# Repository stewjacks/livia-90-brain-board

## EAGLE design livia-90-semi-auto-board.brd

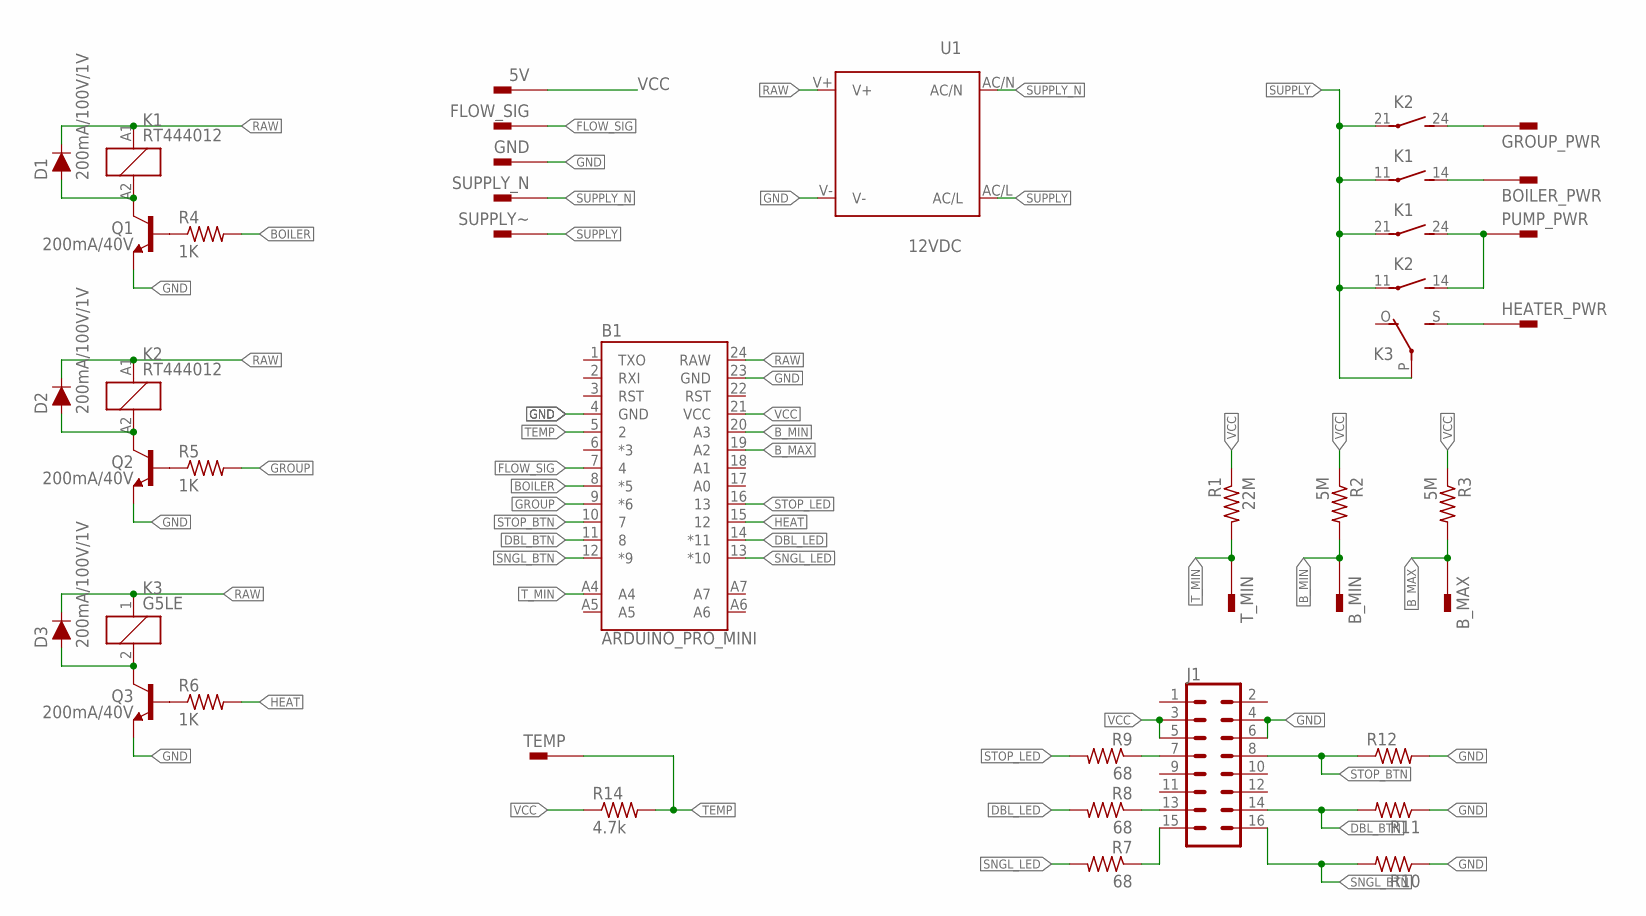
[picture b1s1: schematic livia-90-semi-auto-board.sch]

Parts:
5V: PIN2F061.040; F061.040
B1: ARDUINO_PRO_MINI
BOILER_PWR: PIN2F061.040; F061.040
B_MAX: PIN2F061.040; F061.040
B_MIN: PIN2F061.040; F061.040
D1, D2, D3: 200mA/100V/1V; DIODE-1N4148
FLOW_SIG: PIN2F061.040; F061.040
GND: PIN2F061.040; F061.040
GROUP_PWR: PIN2F061.040; F061.040
HEATER_PWR: PIN2F061.040; F061.040
J1: CONN_08X2; 2X8
K1, K2: RT444012; RT2N/O
K3: G5LE
PUMP_PWR: PIN2F061.040; F061.040
Q1, Q2, Q3: 200mA/40V; TO-92
R1: 22M; 0207/7
R2, R3: 5M; 0207/7
R4, R5, R6: 1K; 0207/7
R7, R8, R9: 68; 0207/7
R10, R11, R12: R-US_0207/7; 0207/7
R14: 4.7k; 0207/7
SUPPLY_N: PIN2F061.040; F061.040
SUPPLY~: PIN2F061.040; F061.040
TEMP: PIN2F061.040; F061.040
T_MIN: PIN2F061.040; F061.040
U1: 12VDC; IRM_05/10

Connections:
BOILER: B1.8 (*5), R4.2
B_MAX: B1.19 (A2), B_MAX.A1, B_MAX.A2, R3.2
B_MIN: B1.20 (A3), B_MIN.A1, B_MIN.A2, R2.2
DBL_BTN: B1.11 (8), J1.14, R11.2
DBL_LED: B1.14 (*11), R8.2
FLOW_SIG: B1.7 (4), FLOW_SIG.A1, FLOW_SIG.A2
GND: B1.4 (GND), B1.23 (GND), GND.A1, GND.A2, J1.4, J1.6, Q1.1 (E), Q2.1 (E), Q3.1 (E), R10.1, R11.1, R12.2, U1.V-
GROUP: B1.9 (*6), R5.2
HEAT: B1.15 (12), R6.2
unnamed: GROUP_PWR.A1, GROUP_PWR.A2, K2.24 (S)
unnamed: Q1.2 (B), R4.1
unnamed: Q2.2 (B), R5.1
unnamed: K1.24 (S), K2.14 (S), PUMP_PWR.A1, PUMP_PWR.A2
unnamed: HEATER_PWR.A1, HEATER_PWR.A2, K3.S
unnamed: Q3.2 (B), R6.1
unnamed: J1.7, R9.1
unnamed: D3.A, K3.2, Q3.3 (C)
unnamed: D2.A, K2.A2 (2), Q2.3 (C)
unnamed: BOILER_PWR.A1, BOILER_PWR.A2, K1.14 (S)
unnamed: D1.A, K1.A2 (2), Q1.3 (C)
unnamed: J1.13, R8.1
unnamed: J1.15, R7.1
RAW: B1.24 (RAW), D1.C, D2.C, D3.C, K1.A1 (1), K2.A1 (1), K3.1, U1.V+
SNGL_BTN: B1.12 (*9), J1.16, R10.2
SNGL_LED: B1.13 (*10), R7.2
STOP_BTN: B1.10 (7), J1.8, R12.1
STOP_LED: B1.16 (13), R9.2
SUPPLY: K1.11, K1.21, K2.11, K2.21, K3.P, SUPPLY~.A1, SUPPLY~.A2, U1.AC/L
SUPPLY_N: SUPPLY_N.A1, SUPPLY_N.A2, U1.AC/N
TEMP: B1.5 (2), R14.2, TEMP.A1, TEMP.A2
T_MIN: B1.A4, R1.2, T_MIN.A1, T_MIN.A2
VCC: 5V.A1, 5V.A2, B1.21 (VCC), J1.3, J1.5, R1.1, R2.1, R3.1, R14.1

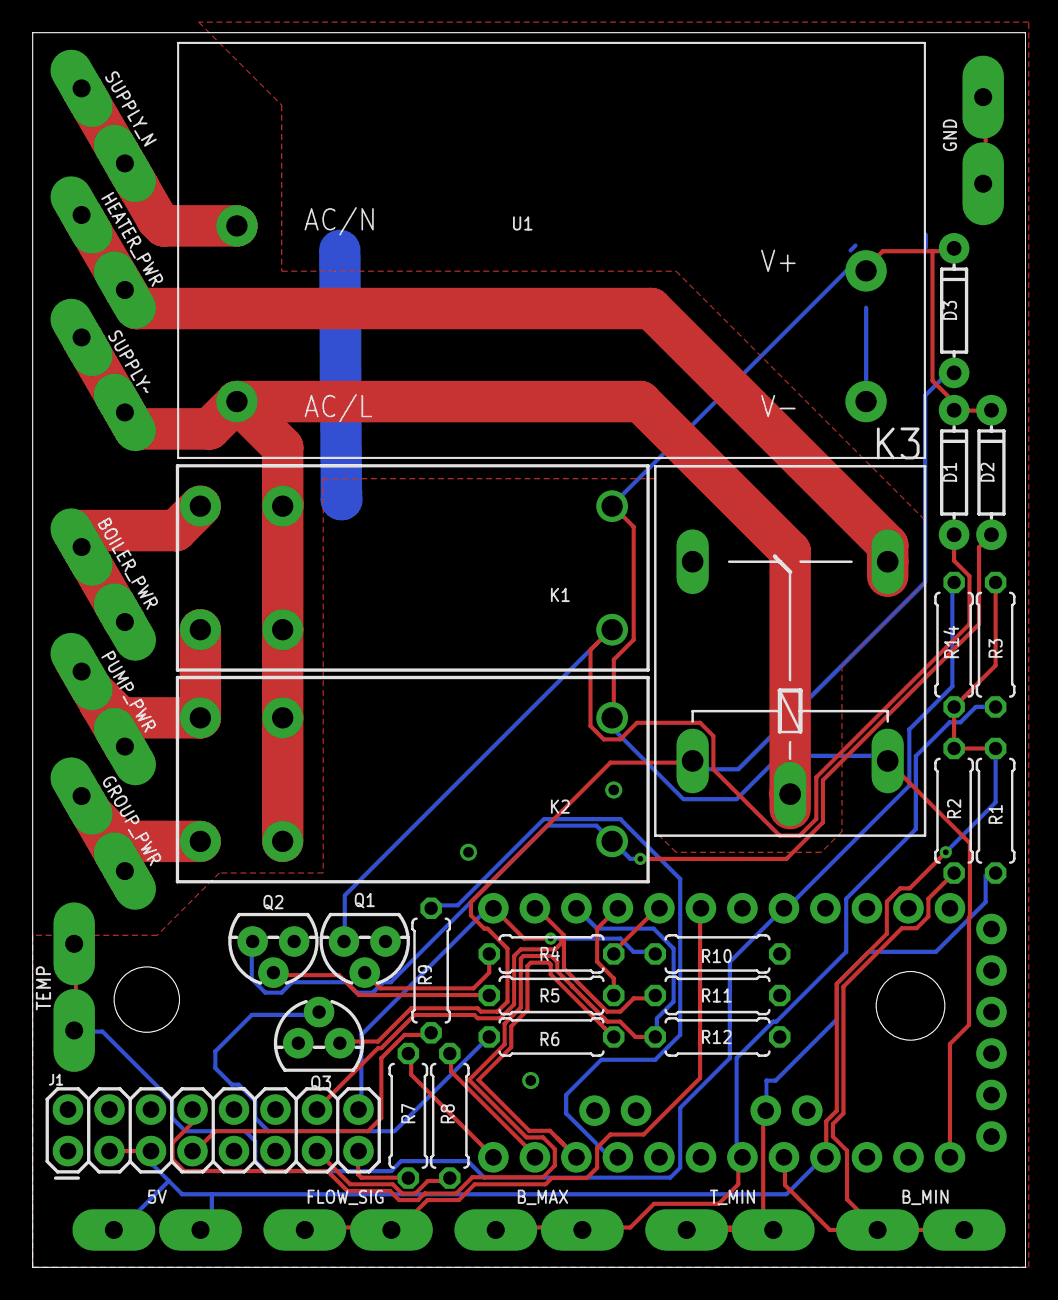
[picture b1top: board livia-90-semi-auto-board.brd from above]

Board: 2 copper layers, 60.8 x 75.6 mm, 38 parts (0 on the bottom side), 32 nets.

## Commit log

2018-04-13 did routing. fixed floating buttons. added drill guide?
2018-04-13 fixed stamping on back
2018-04-14 made an alt board that's smaller and fits in the waterproof box
2018-04-16 added temperature 1line output. This board was sent to production
2018-04-16 removed alternative board (obsolete)

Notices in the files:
parts and their libraries:
SparkFun-Boards: Licensing: Creative Commons ShareAlike 4.0 International - https://creativecommons.org/licenses/by-sa/4.0
